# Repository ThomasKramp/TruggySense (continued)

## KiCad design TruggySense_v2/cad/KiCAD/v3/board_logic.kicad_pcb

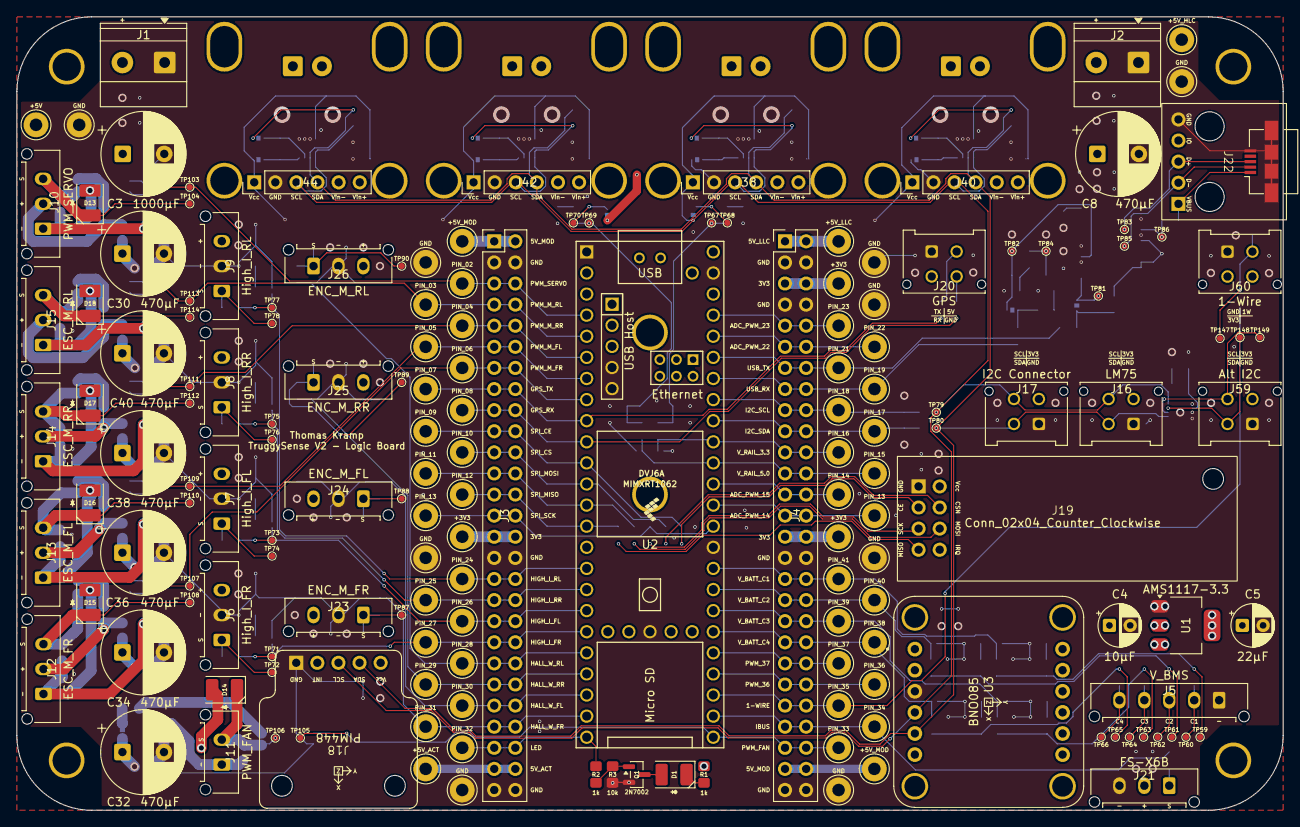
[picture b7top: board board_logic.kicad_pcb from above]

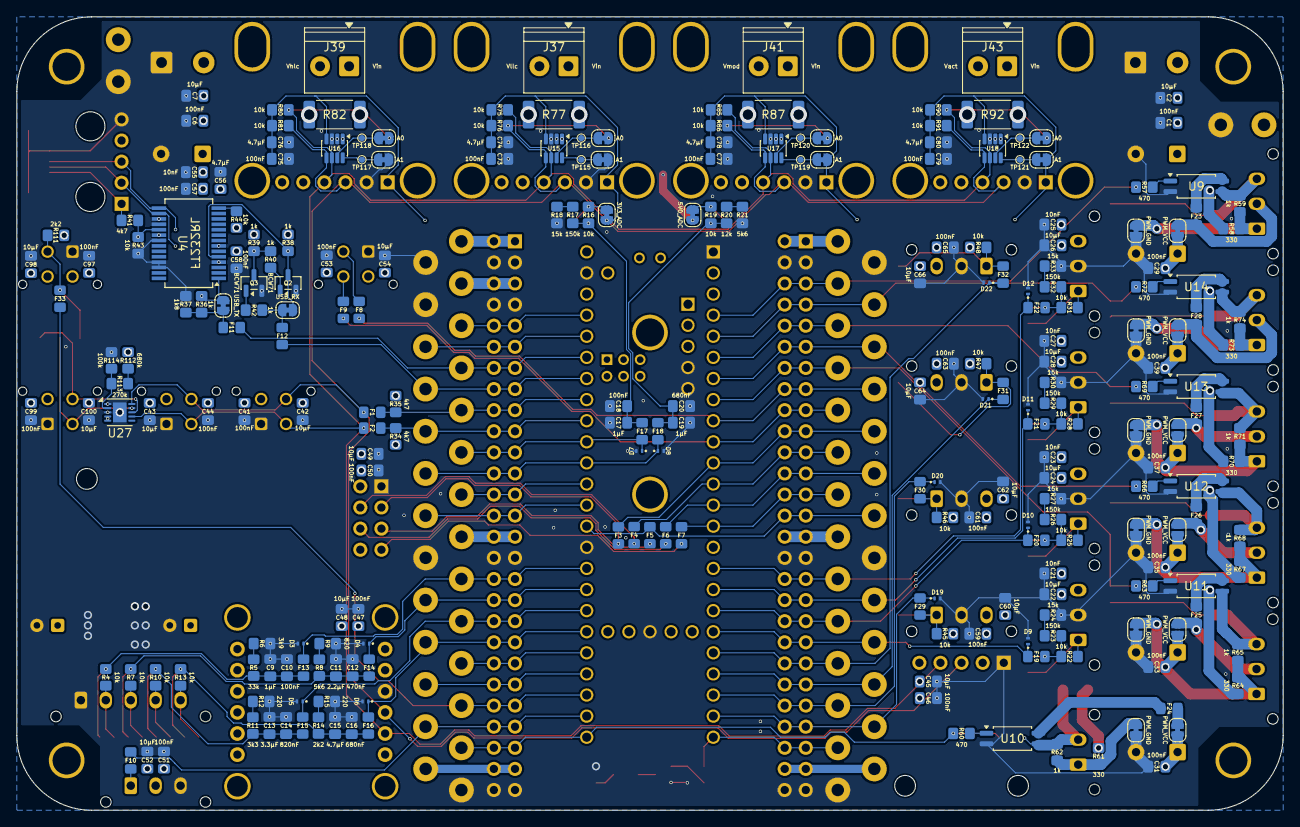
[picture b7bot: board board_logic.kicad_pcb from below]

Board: 6 copper layers, 152.4 x 95.5 mm, 405 parts (244 on the bottom side), 155 nets.

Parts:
C1, C6, C10, C18, C29, C31, C33, C35, C37, C39, C41, C44, C46, C47, C50, C51, C53, C57, C58, C59, C61, C63, C65, C73, C75, C77, C79, C97, C99: 100nF; C_0805_2012Metric_Pad1.18x1.45mm_HandSolder
C2, C7, C22, C24, C26, C28, C42, C43, C45, C48, C49, C52, C54, C60, C62, C64, C66, C98, C100: 10µF; C_0805_2012Metric_Pad1.18x1.45mm_HandSolder
C3: 1000µF; CP_Radial_D10.0mm_P5.00mm
C4: 10µF; CP_Radial_D5.0mm_P2.50mm
C5: 22µF; CP_Radial_D5.0mm_P2.50mm
C8, C30, C32, C34, C36, C38, C40: 470µF; CP_Radial_D10.0mm_P5.00mm
C9, C17, C19: 1µF; C_0805_2012Metric_Pad1.18x1.45mm_HandSolder
C11: 2.2µF; C_0805_2012Metric_Pad1.18x1.45mm_HandSolder
C12: 470nF; C_0805_2012Metric_Pad1.18x1.45mm_HandSolder
C13: 3.3µF; C_0805_2012Metric_Pad1.18x1.45mm_HandSolder
C14: 820nF; C_0805_2012Metric_Pad1.18x1.45mm_HandSolder
C15, C56, C74, C76, C78, C80: 4.7µF; C_0805_2012Metric_Pad1.18x1.45mm_HandSolder
C16, C20: 680nF; C_0805_2012Metric_Pad1.18x1.45mm_HandSolder
C21, C23, C25, C27, C55: 10nF; C_0805_2012Metric_Pad1.18x1.45mm_HandSolder
D1, D13, D14, D15, D16, D17, D18: LED; LED_PLCC-2_3.4x3.0mm_AK
D3, D4, D5, D6, D7, D8, D9, D10, D11, D12, D19, D20, D21, D22: TVS_SMF3.6; Texas_DPY0002A_0.6x1mm_P0.65mm
F1, F2, F3, F4, F5, F6, F7, F8, F9, F10, F11, F12, F13, F14, F15, F16, F17, F18, F19, F20, F21, F22, F23, F24, F25, F26, F27, F28, F29, F30, F31, F32, F33: SMD0805B010TF; Fuse_0805_2012Metric_Pad1.15x1.40mm_HandSolder
J1: TMDC_Input; TerminalBlock_Phoenix_MKDS-1,5-2-5.08_1x02_P5.08mm_Horizont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
J2: Jetson_Connector; TerminalBlock_Phoenix_MKDS-1,5-2-5.08_1x02_P5.08mm_Horizont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
J3, J4: Conn_02x27_Odd_Even; PinHeader_2x27_P2.54mm_Vertical
J5: V_BMS; Molex_Micro-Fit_3.0_43650-0515_1x05_P3.00mm_Vertical
J6: High_I_FR; Molex_Micro-Fit_3.0_43650-0315_1x03_P3.00mm_Vertical
J7: High_I_FL; Molex_Micro-Fit_3.0_43650-0315_1x03_P3.00mm_Vertical
J8: High_I_RR; Molex_Micro-Fit_3.0_43650-0315_1x03_P3.00mm_Vertical
J9: High_I_RL; Molex_Micro-Fit_3.0_43650-0315_1x03_P3.00mm_Vertical
J10: PWM_SERVO; Molex_Micro-Fit_3.0_43650-0315_1x03_P3.00mm_Vertical
J11: PWM_FAN; Molex_Micro-Fit_3.0_43650-0215_1x02_P3.00mm_Vertical
J12: ESC_M_FR; Molex_Micro-Fit_3.0_43650-0315_1x03_P3.00mm_Vertical
J13: ESC_M_FL; Molex_Micro-Fit_3.0_43650-0315_1x03_P3.00mm_Vertical
J14: ESC_M_RR; Molex_Micro-Fit_3.0_43650-0315_1x03_P3.00mm_Vertical
J15: ESC_M_RL; Molex_Micro-Fit_3.0_43650-0315_1x03_P3.00mm_Vertical
J16: LM75; Molex_Micro-Fit_3.0_43045-0412_2x02_P3.00mm_Vertical
J17: I2C Connector; Molex_Micro-Fit_3.0_43045-0412_2x02_P3.00mm_Vertical
J18: PIM448
J19: Conn_02x04_Counter_Clockwise; nRF24L01
J20: GPS; Molex_Micro-Fit_3.0_43045-0412_2x02_P3.00mm_Vertical
J21: FS-X6B; Molex_Micro-Fit_3.0_43650-0315_1x03_P3.00mm_Vertical
J22: Micro_USB; micro_usb_adapter
J23: ENC_M_FR; Molex_Micro-Fit_3.0_43650-0315_1x03_P3.00mm_Vertical
J24: ENC_M_FL; Molex_Micro-Fit_3.0_43650-0315_1x03_P3.00mm_Vertical
J25: ENC_M_RR; Molex_Micro-Fit_3.0_43650-0315_1x03_P3.00mm_Vertical
J26: ENC_M_RL; Molex_Micro-Fit_3.0_43650-0315_1x03_P3.00mm_Vertical
J37, J39, J41, J43: IN; TerminalBlock_Phoenix_PT-1,5-2-3.5-H_1x02_P3.50mm_Horizontal
J38, J40, J42, J44: INA_IO; PinHeader_1x06_P2.54mm_Vertical
J59: Alt I2C; Molex_Micro-Fit_3.0_43045-0412_2x02_P3.00mm_Vertical
J60: 1-Wire; Molex_Micro-Fit_3.0_43045-0412_2x02_P3.00mm_Vertical
JP1: 3V3_ADC; SolderJumper-2_P1.3mm_Bridged_RoundedPad1.0x1.5mm
JP2: 5V0_ADC; SolderJumper-2_P1.3mm_Bridged_RoundedPad1.0x1.5mm
JP3, JP4: PWM_VCC; SolderJumper-2_P1.3mm_Bridged_RoundedPad1.0x1.5mm
JP5, JP6, JP9, JP10, JP13, JP14: PWM_GND; SolderJumper-2_P1.3mm_Bridged_RoundedPad1.0x1.5mm
JP7, JP8, JP11, JP12: PWM_VCC; SolderJumper-2_P1.3mm_Open_RoundedPad1.0x1.5mm
JP15: USB_TX; SolderJumper-2_P1.3mm_Bridged_RoundedPad1.0x1.5mm
JP16: USB_RX; SolderJumper-2_P1.3mm_Bridged_RoundedPad1.0x1.5mm
JP17, JP18, JP19, JP20: A0; SolderJumper-2_P1.3mm_Bridged_RoundedPad1.0x1.5mm
JP21, JP22, JP23, JP24: A1; SolderJumper-2_P1.3mm_Bridged_RoundedPad1.0x1.5mm
Q1: 2N7002; SOT-23
Q2, Q3: BCW71; SOT-23
R1, R2, R36, R38, R39, R40, R42, R59, R62, R65, R68, R71, R74: 1k; R_0805_2012Metric_Pad1.20x1.40mm_HandSolder
R3, R4, R7, R10, R13, R16, R19, R22, R25, R28, R31, R43, R44, R45, R46, R47, R48, R75, R76, R80, R81, R85, R86, R90, R91: 10k; R_0805_2012Metric_Pad1.20x1.40mm_HandSolder
R5: 33k; R_0805_2012Metric_Pad1.20x1.40mm_HandSolder
R6: 3k9; R_0805_2012Metric_Pad1.20x1.40mm_HandSolder
R8, R21: 5k6; R_0805_2012Metric_Pad1.20x1.40mm_HandSolder
R9: 820; R_0805_2012Metric_Pad1.20x1.40mm_HandSolder
R11: 3k3; R_0805_2012Metric_Pad1.20x1.40mm_HandSolder
R12, R15: 220; R_0805_2012Metric_Pad1.20x1.40mm_HandSolder
R14, R111: 2k2; R_0805_2012Metric_Pad1.20x1.40mm_HandSolder
R17, R23, R26, R29, R32: 150k; R_0805_2012Metric_Pad1.20x1.40mm_HandSolder
R18, R24, R27, R30, R33: 15k; R_0805_2012Metric_Pad1.20x1.40mm_HandSolder
R20: 12k; R_0805_2012Metric_Pad1.20x1.40mm_HandSolder
R34, R35, R41: 4k7; R_0805_2012Metric_Pad1.20x1.40mm_HandSolder
R37: 1k8; R_0805_2012Metric_Pad1.20x1.40mm_HandSolder
R57, R60, R63, R66, R69, R72: 470; R_0805_2012Metric_Pad1.20x1.40mm_HandSolder
R58, R61, R64, R67, R70, R73: 330; R_0805_2012Metric_Pad1.20x1.40mm_HandSolder
R77, R82, R87, R92: 100m; R_2512_6332Metric_Pad1.40x3.35mm_HandSolder
R112: 680k; R_0805_2012Metric_Pad1.20x1.40mm_HandSolder
R113: 270k; R_0805_2012Metric_Pad1.20x1.40mm_HandSolder
R114: 100k; R_0805_2012Metric_Pad1.20x1.40mm_HandSolder
TP1: +5V; Pin_D1.3mm_L11.0mm
TP2, TP4, TP7, TP8, TP12, TP35, TP36, TP57, TP58: GND; Pin_D1.3mm_L11.0mm
TP3: +5V_HLC; Pin_D1.3mm_L11.0mm
TP5, TP56: +5V_MOD; Pin_D1.3mm_L11.0mm
TP6: +5V_LLC; Pin_D1.3mm_L11.0mm
TP9: PIN_02; Pin_D1.3mm_L11.0mm
TP10, TP33, TP34: +3V3; Pin_D1.3mm_L11.0mm
TP11: PIN_03; Pin_D1.3mm_L11.0mm
TP13: PIN_04; Pin_D1.3mm_L11.0mm
TP14: PIN_23; Pin_D1.3mm_L11.0mm
TP15: PIN_05; Pin_D1.3mm_L11.0mm
TP16: PIN_22; Pin_D1.3mm_L11.0mm
TP17: PIN_06; Pin_D1.3mm_L11.0mm
TP18: PIN_21; Pin_D1.3mm_L11.0mm
TP19: PIN_07; Pin_D1.3mm_L11.0mm
TP20: PIN_19; Pin_D1.3mm_L11.0mm
TP21: PIN_08; Pin_D1.3mm_L11.0mm
TP22: PIN_18; Pin_D1.3mm_L11.0mm
TP23: PIN_09; Pin_D1.3mm_L11.0mm
TP24: PIN_17; Pin_D1.3mm_L11.0mm
TP25: PIN_10; Pin_D1.3mm_L11.0mm
TP26: PIN_16; Pin_D1.3mm_L11.0mm
TP27: PIN_11; Pin_D1.3mm_L11.0mm
TP28: PIN_15; Pin_D1.3mm_L11.0mm
TP29: PIN_12; Pin_D1.3mm_L11.0mm
TP30: PIN_14; Pin_D1.3mm_L11.0mm
TP31, TP32: PIN_13; Pin_D1.3mm_L11.0mm
TP37: PIN_24; Pin_D1.3mm_L11.0mm
TP38: PIN_41; Pin_D1.3mm_L11.0mm
TP39: PIN_25; Pin_D1.3mm_L11.0mm
TP40: PIN_40; Pin_D1.3mm_L11.0mm
TP41: PIN_26; Pin_D1.3mm_L11.0mm
TP42: PIN_39; Pin_D1.3mm_L11.0mm
TP43: PIN_27; Pin_D1.3mm_L11.0mm
TP44: PIN_38; Pin_D1.3mm_L11.0mm
TP45: PIN_28; Pin_D1.3mm_L11.0mm
TP46: PIN_37; Pin_D1.3mm_L11.0mm
TP47: PIN_29; Pin_D1.3mm_L11.0mm
TP48: PIN_36; Pin_D1.3mm_L11.0mm
TP49: PIN_30; Pin_D1.3mm_L11.0mm
TP50: PIN_35; Pin_D1.3mm_L11.0mm
TP51: PIN_31; Pin_D1.3mm_L11.0mm
TP52: PIN_34; Pin_D1.3mm_L11.0mm
TP53: PIN_32; Pin_D1.3mm_L11.0mm
TP54: PIN_33; Pin_D1.3mm_L11.0mm
TP55: +5V_ACT; Pin_D1.3mm_L11.0mm
TP59, TP60, TP61, TP62, TP63, TP64, TP65, TP66, TP67, TP68, TP69, TP70, TP71, TP72, TP73, TP74, TP75, TP76, TP77, TP78, TP79, TP80, TP81, TP82, TP83, TP84, TP85, TP86, TP87, TP88, TP89, TP90, TP103, TP104, TP105, TP106, TP107, TP108, TP109, TP110, TP111, TP112, TP113, TP114, TP115, TP116, TP117, TP118, TP119, TP120, TP121, TP122, TP147, TP148, TP149: TestPoint; TestPad
U1: AMS1117-3.3; SOT-223-3_TabPin2
U2: Teensy4.1; Teensy41
U3: BNO085
U4: FT232RL; SSOP-28_5.3x10.2mm_P0.65mm
U9, U10, U11, U12, U13, U14: VOS618A; SSOP-4_4.4x2.6mm_P1.27mm
U15, U16, U17, U18: INA219AxDCN; SOT-23-8
U27: LTC4316xDD; DFN-10-1EP_3x3mm_P0.5mm_EP1.65x2.38mm

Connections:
1-Wire: F33.1, J4.45, J4.46, TP50.1, U2.27 (35_TX8)
+3V3: C5.1, C41.1, C42.1, C43.1, C44.1, C45.1, C46.1, C49.1, C50.1, C58.1, C59.1, C60.1, C61.1, C62.1, C63.1, C64.1, C65.1, C66.1, C73.1, C74.1, C75.1, C76.1, C77.1, C78.1, C79.1, C80.1, C97.1, C98.1, C99.1, C100.1, J3.29, J3.30, J4.5, J4.6, J4.29, J4.30, J16.3, J17.3, J18.5, J19.2, J23.3, J24.3, J25.3, J26.3, J38.1, J40.1, J42.1, J44.1, J59.3, J60.3, JP1.2 (B), JP23.1 (A), JP24.1 (A), R1.2, R34.2, R35.1, R44.1, R45.2, R46.2, R47.2, R48.2, R75.1, R76.1, R80.1, R81.1, R85.1, R86.1, R90.1, R91.1, R111.1, R112.2, TP10.1, TP33.1, TP34.1, U1.2 (VO), U4.4 (VCCIO), U4.17 (3V3OUT), U15.4 (VS), U16.4 (VS), U17.4 (VS), U18.4 (VS), U27.4 (V_{CC}), U27.5 (ENABLE)
+5V: C1.1, C2.1, C3.1, J1.2, J37.1, J38.6, J39.1, J40.6, J41.1, J42.6, J43.1, J44.6, JP2.2 (B), R77.1, R82.1, R87.1, R92.1, TP1.1, U15.1 (IN+), U16.1 (IN+), U17.1 (IN+), U18.1 (IN+)
+5V_ACT: C29.1, C30.1, C31.1, C32.1, C33.1, C34.1, C35.1, C36.1, C37.1, C38.1, C39.1, C40.1, J3.51, J3.52, J43.2, J44.5, JP3.1 (A), JP4.1 (A), JP7.1 (A), JP8.1 (A), JP11.1 (A), JP12.1 (A), R92.2, TP55.1, U18.2 (IN-)
+5V_HLC: C6.1, C7.1, C8.1, C55.1, C56.1, C57.1, J2.2, J39.2, J40.5, R38.2, R39.1, R82.2, TP3.1, U4.20 (VCC), U16.2 (IN-)
+5V_LLC: J4.1, J4.2, J37.2, J38.5, R77.2, TP6.1, U2.48 (VIN), U2.49 (VUSB), U15.2 (IN-)
+5V_MOD: C4.1, C21.2, C22.2, C23.2, C24.2, C25.2, C26.2, C27.2, C28.2, C47.1, C48.1, C51.1, C52.1, C53.1, C54.1, J3.1, J3.2, J4.51, J4.52, J6.3, J7.3, J8.3, J9.3, J20.3, J21.2, J41.2, J42.5, R87.2, TP5.1, TP56.1, U1.3 (VI), U3.JP1_1 (VIN), U17.2 (IN-)
/Analog Inputs/ADC Protection 1/IN: C9.1, C10.1, F13.1, R4.2, R5.1, TP59.1
/Analog Inputs/ADC Protection 2/IN: C11.1, C12.1, F14.1, R7.2, R8.1, TP61.1
/Analog Inputs/ADC Protection 3/IN: C13.1, C14.1, F15.1, R10.2, R11.1, TP63.1
/Analog Inputs/ADC Protection 4/IN: C15.1, C16.1, F16.1, R13.2, R14.1, TP65.1
/Analog Inputs/ADC Protection 5/IN: C17.2, C18.1, F17.1, R16.2, R17.1, TP67.1
/Analog Inputs/ADC Protection 6/IN: C19.2, C20.1, F18.1, R19.2, R20.1, TP69.1
/Analog Inputs/ADC Protection 7/IN: F19.1, R22.2, R23.1, TP71.1
/Analog Inputs/ADC Protection 8/IN: F20.1, R25.2, R26.1, TP73.1
/Analog Inputs/ADC Protection 9/IN: F21.1, R28.2, R29.1, TP75.1
/Analog Inputs/ADC Protection 10/IN: F22.1, R31.2, R32.1, TP77.1
/I2C Modules/Low Current Sensor - ACT/A0: F2.2, J16.2, J17.2, J18.4, J38.4, J40.4, J42.4, J44.4, JP18.1 (A), JP20.1 (A), R75.2, R80.2, R85.2, R90.2, TP80.1, U3.JP1_5 (SDA), U15.6 (SDA), U16.6 (SDA), U17.6 (SDA), U18.6 (SDA), U27.7 (SDAIN)
/I2C Modules/Low Current Sensor - ACT/SCL: F1.1, J16.4, J17.4, J18.3, J38.3, J40.3, J42.3, J44.3, JP17.1 (A), JP19.1 (A), R76.2, R81.2, R86.2, R91.2, TP79.1, U3.JP1_4 (SCL), U15.5 (SCL), U16.5 (SCL), U17.5 (SCL), U18.5 (SCL), U27.10 (SCLIN)
/PWM Outputs/PWM Output Protection 1/GND_OUT: J10.1, JP5.1 (A), R58.2, R59.2
/PWM Outputs/PWM Output Protection 1/OUT: D13.2 (A), J10.3, R59.1, TP104.1, U9.3
/PWM Outputs/PWM Output Protection 1/VCC_OUT: F23.2, J10.2, JP3.2 (B)
/PWM Outputs/PWM Output Protection 2/GND_OUT: J11.1, JP6.1 (A), R61.2, R62.2
/PWM Outputs/PWM Output Protection 2/OUT: D14.2 (A), J11.2, R62.1, TP106.1, U10.3
/PWM Outputs/PWM Output Protection 2/VCC_OUT: F24.2, JP4.2 (B)
/PWM Outputs/PWM Output Protection 3/GND_OUT: J12.1, JP9.1 (A), R64.2, R65.2
/PWM Outputs/PWM Output Protection 3/OUT: D15.2 (A), J12.3, R65.1, TP108.1, U11.3
/PWM Outputs/PWM Output Protection 3/VCC_OUT: F25.2, J12.2, JP7.2 (B)
/PWM Outputs/PWM Output Protection 4/GND_OUT: J13.1, JP10.1 (A), R67.2, R68.2
/PWM Outputs/PWM Output Protection 4/OUT: D16.2 (A), J13.3, R68.1, TP110.1, U12.3
/PWM Outputs/PWM Output Protection 4/VCC_OUT: F26.2, J13.2, JP8.2 (B)
/PWM Outputs/PWM Output Protection 5/GND_OUT: J14.1, JP13.1 (A), R70.2, R71.2
/PWM Outputs/PWM Output Protection 5/OUT: D17.2 (A), J14.3, R71.1, TP112.1, U13.3
/PWM Outputs/PWM Output Protection 5/VCC_OUT: F27.2, J14.2, JP11.2 (B)
/PWM Outputs/PWM Output Protection 6/GND_OUT: J15.1, JP14.1 (A), R73.2, R74.2
/PWM Outputs/PWM Output Protection 6/OUT: D18.2 (A), J15.3, R74.1, TP114.1, U14.3
/PWM Outputs/PWM Output Protection 6/VCC_OUT: F28.2, J15.2, JP12.2 (B)
/Various Inputs/ISR Protection 1/IN: F29.1, J23.1, R45.1, TP87.1
/Various Inputs/ISR Protection 2/IN: F30.1, J24.1, R46.1, TP88.1
/Various Inputs/ISR Protection 3/IN: F31.1, J25.1, R47.1, TP89.1
/Various Inputs/ISR Protection 4/IN: F32.1, J26.1, R48.1, TP90.1
ADC_I_M_FL: D10.1 (K), F20.2, J3.37, J3.38, TP41.1, U2.18 (26_A12_MOSI1)
ADC_I_M_FR: D9.1 (K), F19.2, J3.39, J3.40, TP43.1, U2.19 (27_A13_SCK1)
ADC_I_M_RL: D12.1 (K), F22.2, J3.33, J3.34, TP37.1, U2.16 (24_A10_TX6_SCL2)
ADC_I_M_RR: D11.1 (K), F21.2, J3.35, J3.36, TP39.1, U2.17 (25_A11_RX6_SDA2)
ADC_PWM_14: J4.27, J4.28, TP32.1, U2.36 (14_A0_TX3_SPDIF_OUT)
ADC_PWM_15: J4.25, J4.26, TP30.1, U2.37 (15_A1_RX3_SPDIF_IN)
ADC_PWM_22: J4.11, J4.12, TP16.1, U2.44 (22_A8_CTX1)
ADC_PWM_23: J4.9, J4.10, TP14.1, U2.45 (23_A9_CRX1_MCLK1)
ADC_V_3.3: D7.1 (K), F17.2, J4.21, J4.22, TP26.1, U2.39 (17_A3_TX4_SDA1)
ADC_V_5.0: D8.1 (K), F18.2, J4.23, J4.24, TP28.1, U2.38 (16_A2_RX4_SCL1)
ADC_V_B_C1: D3.1 (K), F13.2, J4.33, J4.34, TP38.1, U2.33 (41_A17)
ADC_V_B_C2: D4.1 (K), F14.2, J4.35, J4.36, TP40.1, U2.32 (40_A16)
ADC_V_B_C3: D5.1 (K), F15.2, J4.37, J4.38, TP42.1, U2.31 (39_MISO1_OUT1A)
ADC_V_B_C4: D6.1 (K), F16.2, J4.39, J4.40, TP44.1, U2.30 (38_CS1_IN1)
GND: C1.2, C2.2, C3.2, C4.2, C5.2, C6.2, C7.2, C8.2, C9.2, C10.2, C11.2, C12.2, C13.2, C14.2, C15.2, C16.2, C17.1, C18.2, C19.1, C20.2, C21.1, C22.1, C23.1, C24.1, C25.1, C26.1, C27.1, C28.1, C29.2, C30.2, C31.2, C32.2, C33.2, C34.2, C35.2, C36.2, C37.2, C38.2, C39.2, C40.2, C41.2, C42.2, C43.2, C44.2, C45.2, C46.2, C47.2, C48.2, C49.2, C50.2, C51.2, C52.2, C53.2, C54.2, C55.2, C56.2, C57.2, C58.2, C59.2, C60.2, C61.2, C62.2, C63.2, C64.2, C65.2, C66.2, C73.2, C74.2, C75.2, C76.2, C77.2, C78.2, C79.2, C80.2, C97.2, C98.2, C99.2, C100.2, D3.2 (A), D4.2 (A), D5.2 (A), D6.2 (A), D7.2 (A), D8.2 (A), D9.2 (A), D10.2 (A), D11.2 (A), D12.2 (A), D19.2 (A), D20.2 (A), D21.2 (A), D22.2 (A), J1.1, J2.1, J3.3, J3.4, J3.31, J3.32, J3.53, J3.54, J4.3, J4.4, J4.7, J4.8, J4.31, J4.32, J4.53, J4.54, J5.1, J6.2, J7.2, J8.2, J9.2, J16.1, J17.1, J18.1, J19.1, J20.1, J21.3, J22.5, J23.2, J24.2, J25.2, J26.2, J38.2, J40.2, J42.2, J44.2, J59.1, J60.1, JP5.2 (B), JP6.2 (B), JP9.2 (B), JP10.2 (B), JP13.2 (B), JP14.2 (B), JP21.1 (A), JP22.1 (A), Q1.2 (S), Q2.2 (E), Q3.2 (E), R3.2, R6.2, R9.2, R12.2, R15.2, R18.2, R21.2, R24.2, R27.2, R30.2, R33.2, R37.1, R43.2, R114.1, TP2.1, TP4.1, TP7.1, TP8.1, TP12.1, TP35.1, TP36.1, TP57.1, TP58.1, U1.1 (GND), U2.1 (GND), U2.34 (GND), U2.47 (GND), U2.52 (GND), U2.58 (GND), U2.59 (GND), U3.JP1_3 (GND), U4.7 (GND), U4.18 (GND), U4.21 (GND), U4.25 (AGND), U4.26 (TEST), U9.2, U10.2, U11.2, U12.2, U13.2, U14.2, U15.3 (GND), U16.3 (GND), U17.3 (GND), U18.3 (GND), U27.1 (GND), U27.3 (XORL), U27.11 (EP)
HALL_W_FL: D20.1 (K), F30.2, J3.45, J3.46, TP49.1, U2.22 (30_CRX3)
HALL_W_FR: D19.1 (K), F29.2, J3.47, J3.48, TP51.1, U2.23 (31_CTX3)
HALL_W_RL: D22.1 (K), F32.2, J3.41, J3.42, TP45.1, U2.20 (28_RX7)
HALL_W_RR: D21.1 (K), F31.2, J3.43, J3.44, TP47.1, U2.21 (29_TX7)
I2C_SCL: F1.2, J4.17, J4.18, R35.2, TP22.1, U2.41 (19_A5_SCL)
I2C_SDA: F2.1, J4.19, J4.20, R34.1, TP24.1, U2.40 (18_A4_SDA)
LED: J3.49, J3.50, R2.1, TP53.1, U2.24 (32_OUT1B)
unnamed: D1.2 (A), R1.1
unnamed: D1.1 (K), Q1.3 (D)
unnamed: D13.1 (K), R58.1
unnamed: D14.1 (K), R61.1
unnamed: D15.1 (K), R64.1
unnamed: D16.1 (K), R67.1
unnamed: D17.1 (K), R70.1
unnamed: D18.1 (K), R73.1
unnamed: F23.1, U9.4
unnamed: F24.1, U10.4
unnamed: F25.1, U11.4
unnamed: F26.1, U12.4
unnamed: F27.1, U13.4
unnamed: F28.1, U14.4
unnamed: J5.2, R4.1, TP60.1
unnamed: J5.3, R7.1, TP62.1
unnamed: J5.4, R10.1, TP64.1
unnamed: J5.5, R13.1, TP66.1
unnamed: J6.1, R22.1, TP72.1
unnamed: J7.1, R25.1, TP74.1
unnamed: J8.1, R28.1, TP76.1
unnamed: J9.1, R31.1, TP78.1
unnamed: F3.1, J19.3
unnamed: F4.1, J19.4
unnamed: F5.1, J19.5
unnamed: F6.1, J19.6
unnamed: F7.1, J19.7
unnamed: F8.2, J20.2
unnamed: F9.2, J20.4
unnamed: F10.1, J21.1
unnamed: J22.1, R41.2
unnamed: J22.2, TP85.1, U4.16 (USBD-)
unnamed: J22.3, TP83.1, U4.15 (USBD+)
unnamed: J59.2, TP148.1, U27.9 (SCLOUT)
unnamed: J59.4, TP149.1, U27.8 (SDAOUT)
unnamed: F33.2, J60.2, R111.2, TP147.1
unnamed: JP1.1 (A), R16.1, TP68.1
unnamed: JP2.1 (A), R19.1, TP70.1
unnamed: F11.2, JP15.1 (A), R36.1, R37.2
unnamed: JP15.2 (B), R36.2, TP81.1, U4.1 (TXD)
unnamed: F12.2, JP16.1 (A), R42.2
unnamed: JP16.2 (B), Q2.3 (C), R38.1, TP82.1, U4.5 (RXD)
unnamed: JP17.2 (B), TP116.1, U15.7 (A0)
unnamed: JP18.2 (B), TP118.1, U16.7 (A0)
unnamed: JP19.2 (B), TP120.1, U17.7 (A0)
unnamed: JP20.2 (B), TP122.1, U18.7 (A0)
unnamed: JP21.2 (B), TP115.1, U15.8 (A1)
unnamed: JP22.2 (B), TP117.1, U16.8 (A1)
unnamed: JP23.2 (B), TP119.1, U17.8 (A1)
unnamed: JP24.2 (B), TP121.1, U18.8 (A1)
unnamed: Q1.1 (G), R2.2, R3.1
unnamed: Q2.1 (B), R40.1
unnamed: Q3.1 (B), R42.1
unnamed: Q3.3 (C), R39.2, R40.2, TP84.1
unnamed: R5.2, R6.1
unnamed: R8.2, R9.1
unnamed: R11.2, R12.1
unnamed: R14.2, R15.1
unnamed: R17.2, R18.1
unnamed: R20.2, R21.1
unnamed: R23.2, R24.1
unnamed: R26.2, R27.1
unnamed: R29.2, R30.1
unnamed: R32.2, R33.1
unnamed: R57.2, U9.1
unnamed: R60.2, U10.1
unnamed: R63.2, U11.1
unnamed: R66.2, U12.1
unnamed: R69.2, U13.1
unnamed: R72.2, U14.1
unnamed: R112.1, R113.2
unnamed: R44.2, U4.14 (CBUS3)
unnamed: R41.1, R43.1, TP86.1, U4.19 (~RESET)
unnamed: R113.1, R114.2, U27.2 (XORH)
PWM_36: J4.43, J4.44, TP48.1, U2.28 (36_CS)
PWM_37: J4.41, J4.42, TP46.1, U2.29 (37_CS)
PWM_FAN: J4.49, J4.50, R60.1, TP54.1, TP105.1, U2.25 (33_MCLK2)
PWM_M_FL: J3.11, J3.12, R66.1, TP15.1, TP109.1, U2.7 (5_IN2)
PWM_M_FR: J3.13, J3.14, R63.1, TP17.1, TP107.1, U2.8 (6_OUT1D)
PWM_M_RL: J3.7, J3.8, R72.1, TP11.1, TP113.1, U2.5 (3_LRCLK2)
PWM_M_RR: J3.9, J3.10, R69.1, TP13.1, TP111.1, U2.6 (4_BCLK2)
PWM_SERVO: J3.5, J3.6, R57.1, TP9.1, TP103.1, U2.4 (2_OUT2)
SPI_CE: F3.2, J3.19, J3.20, TP23.1, U2.11 (9_OUT1C)
SPI_CS: F4.2, J3.21, J3.22, TP25.1, U2.12 (10_CS_MQSR)
SPI_MISO: F7.2, J3.25, J3.26, TP29.1, U2.14 (12_MISO_MQSL)
SPI_MOSI: F6.2, J3.23, J3.24, TP27.1, U2.13 (11_MOSI_CTX1)
SPI_SCK: F5.2, J3.27, J3.28, TP31.1, U2.35 (13_SCK_LED)
UART_GPS_RX: F9.1, J3.17, J3.18, TP21.1, U2.10 (8_TX2_IN1)
UART_GPS_TX: F8.1, J3.15, J3.16, TP19.1, U2.9 (7_RX2_OUT1A)
UART_IBUS_TX: F10.2, J4.47, J4.48, TP52.1, U2.26 (34_RX8)
UART_USB_RX: F12.1, J4.15, J4.16, TP20.1, U2.42 (20_A6_TX5_LRCLK1)
UART_USB_TX: F11.1, J4.13, J4.14, TP18.1, U2.43 (21_A7_RX5_BCLK1)

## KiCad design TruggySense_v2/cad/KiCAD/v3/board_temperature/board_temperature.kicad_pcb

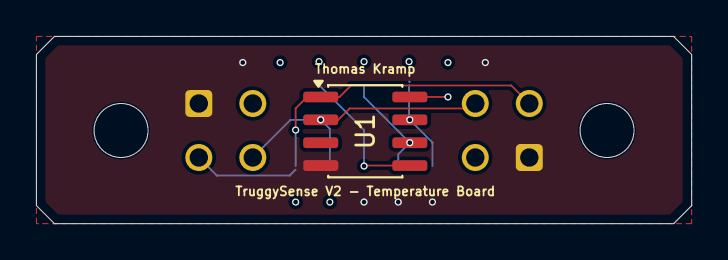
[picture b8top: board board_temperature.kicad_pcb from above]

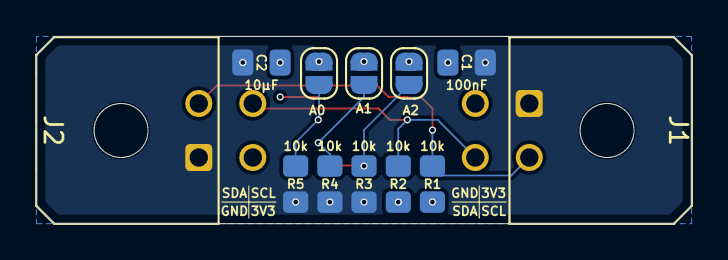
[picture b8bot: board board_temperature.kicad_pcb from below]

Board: 6 copper layers, 36.4 x 10.4 mm, 13 parts (12 on the bottom side), 7 nets.

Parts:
C1: 100nF; C_0805_2012Metric_Pad1.18x1.45mm_HandSolder
C2: 10µF; C_0805_2012Metric_Pad1.18x1.45mm_HandSolder
J1: I2C_INPUT; Molex_Micro-Fit_3.0_43045-0400_2x02_P3.00mm_Horizontal
J2: I2C_OUTPUT; Molex_Micro-Fit_3.0_43045-0400_2x02_P3.00mm_Horizontal
JP1: A2; SolderJumper-2_P1.3mm_Open_RoundedPad1.0x1.5mm
JP2: A1; SolderJumper-2_P1.3mm_Open_RoundedPad1.0x1.5mm
JP3: A0; SolderJumper-2_P1.3mm_Open_RoundedPad1.0x1.5mm
R1, R2, R3, R4, R5: 10k; R_0805_2012Metric_Pad1.20x1.40mm_HandSolder
U1: LM75B; SOIC-8_3.9x4.9mm_P1.27mm

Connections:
+3V3: C1.2, C2.2, J1.3, J2.3, JP1.2 (B), JP2.2 (B), JP3.2 (B), R1.2, R2.2, U1.8 (+Vs)
GND: C1.1, C2.1, J1.1, J2.1, R3.1, R4.1, R5.1, U1.4 (GND)
unnamed: J1.2, J2.2, R1.1, U1.1 (SDA)
unnamed: J1.4, J2.4, R2.1, U1.2 (SCL)
unnamed: JP1.1 (A), R3.2, U1.5 (A2)
unnamed: JP2.1 (A), R4.2, U1.6 (A1)
unnamed: JP3.1 (A), R5.2, U1.7 (A0)
